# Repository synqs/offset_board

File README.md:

# offset_board
 A precise offset board used for active magnetic field control.

# Main component: AD524 and AD588 

# FEATURES:

Low drift: 1.5 ppm/°C
Low initial error: 1 mV
Pin programmable output
+10 V, +5 V, ±5 V tracking, −5 V, −10 V
Flexible output force and sense terminals
High impedance ground sense
Compact and easy to assemble
Expensive (good stuff never comes cheap)

# GENERAL DESCRIPTION: 

This board takes in a signal between 0 and 5V which then can be subtracted by a DC voltage provided by AD588 between 0 and 5V set by the poti R2 and then amplified by the AD524. The amplification factor can be set to 10,100 or 1000. 

# SPECIFICATIONS
Typical at 25°C, -12 V to 12 V output, VS = ±15 V, unless otherwise noted.

# REVISION HISTORY

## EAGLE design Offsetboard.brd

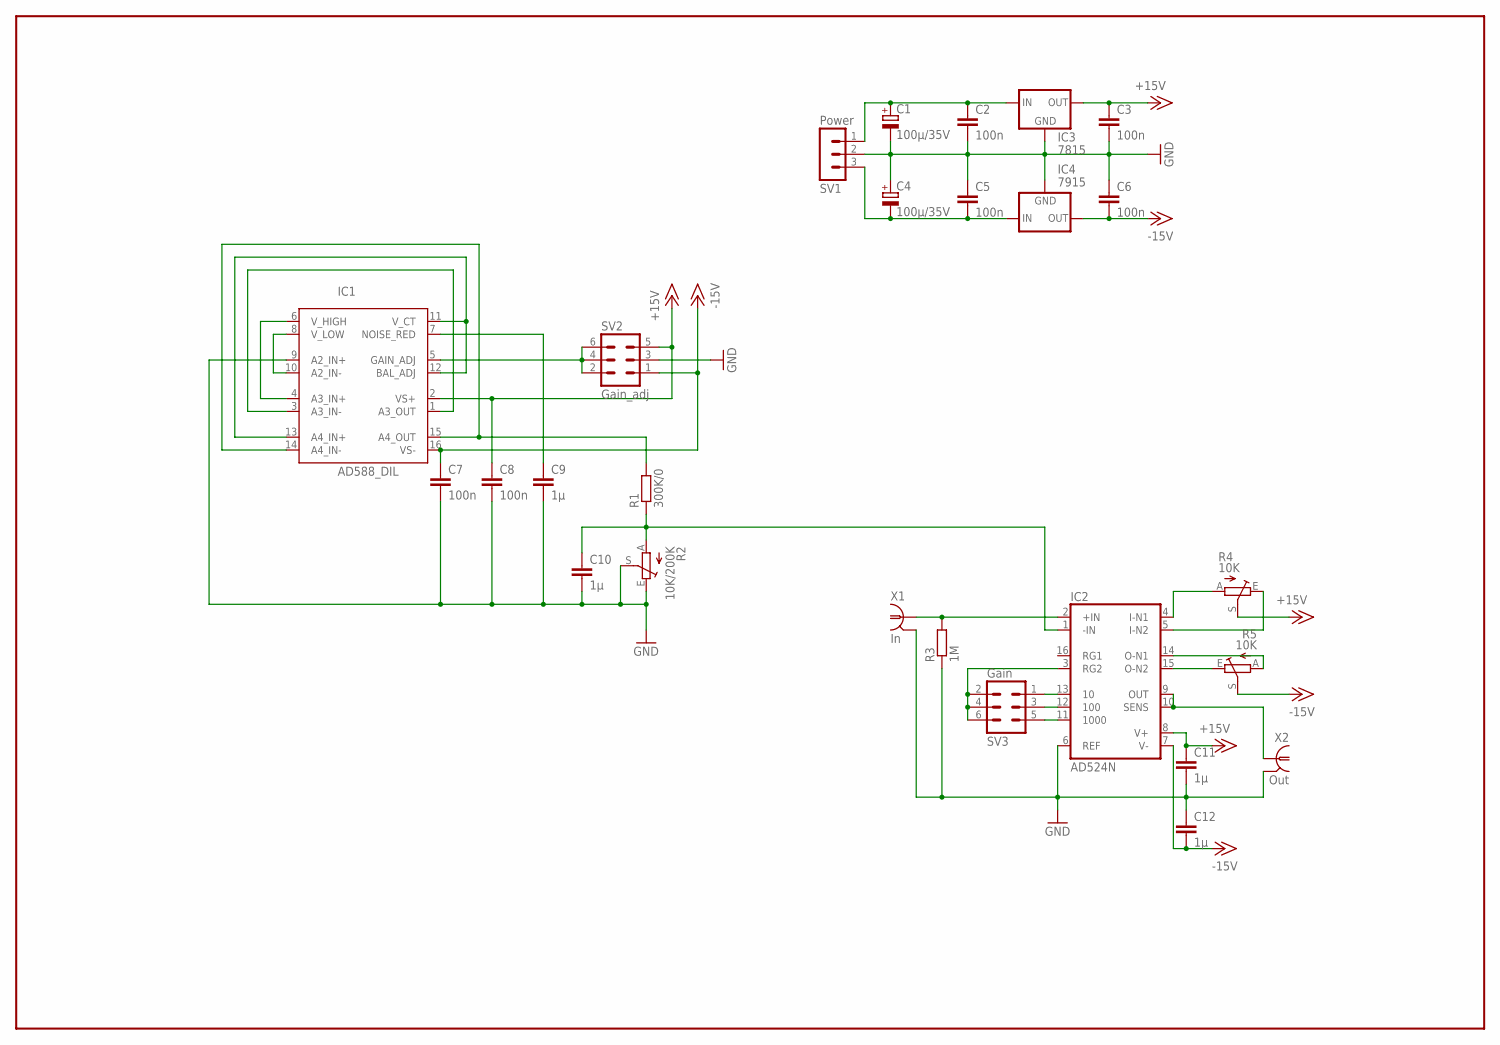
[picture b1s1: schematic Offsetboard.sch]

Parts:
C1, C4: 100µ/35V; E2,5-6
C2, C3, C5, C6, C7, C8: 100n; C1206K
C9, C10, C11, C12: 1µ; C1206K
IC1: AD588_DIL; DIL16
IC2: AD524N; DIL16
IC3: 7815; 78MXXS
IC4: 7915; 79XXS
R1: 300K/0; 0207/10
R2: 10K/200K; S64W
R3: 1M; 0207/10
R4, R5: 10K; S64W
SV1: Power; MA03-1
SV2: Gain_adj; MA03-2
SV3: Gain; MA03-2
X1: In; AMP_227161
X2: Out; AMP_227161

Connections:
+15V: C3.1, C8.1, C11.1, IC1.2 (VS+), IC2.8 (V+), IC3.OUT, R4.S, SV2.5
-15V: C6.2, C7.1, C12.2, IC1.16 (VS-), IC2.7 (V-), IC4.OUT, R5.S, SV2.1
GND: C1.-, C2.2, C3.2, C4.+, C5.1, C6.1, C7.2, C8.2, C9.2, C10.2, C11.2, C12.1, IC1.9 (A2_IN+), IC2.6 (REF), IC3.GND, IC4.GND, R2.E, R2.S, R3.1, SV1.2, SV2.3, X1.2 (GND), X2.2 (GND)
unnamed: IC2.4 (I-N1), R4.A
unnamed: IC2.15 (O-N2), R5.E
unnamed: IC2.14 (O-N1), R5.A
unnamed: IC2.5 (I-N2), R4.E
unnamed: IC2.2 (+IN), R3.2, X1.1
unnamed: IC2.13 (10), SV3.1
unnamed: IC2.12 (100), SV3.3
unnamed: IC2.11 (1000), SV3.5
unnamed: IC2.3 (RG2), SV3.2, SV3.4, SV3.6
unnamed: IC2.9 (OUT), IC2.10 (SENS), X2.1
unnamed: IC1.14 (A4_IN-), IC1.15 (A4_OUT), R1.2
unnamed: C10.1, IC2.1 (-IN), R1.1, R2.A
unnamed: IC1.1 (A3_OUT), IC1.3 (A3_IN-)
unnamed: IC1.4 (A3_IN+), IC1.6 (V_HIGH)
unnamed: C9.1, IC1.7 (NOISE_RED)
unnamed: IC1.8 (V_LOW), IC1.10 (A2_IN-)
unnamed: IC1.11 (V_CT), IC1.12 (BAL_ADJ), IC1.13 (A4_IN+)
unnamed: C4.-, C5.2, IC4.IN, SV1.3
unnamed: IC1.5 (GAIN_ADJ), SV2.2, SV2.4, SV2.6
unnamed: C1.+, C2.1, IC3.IN, SV1.1

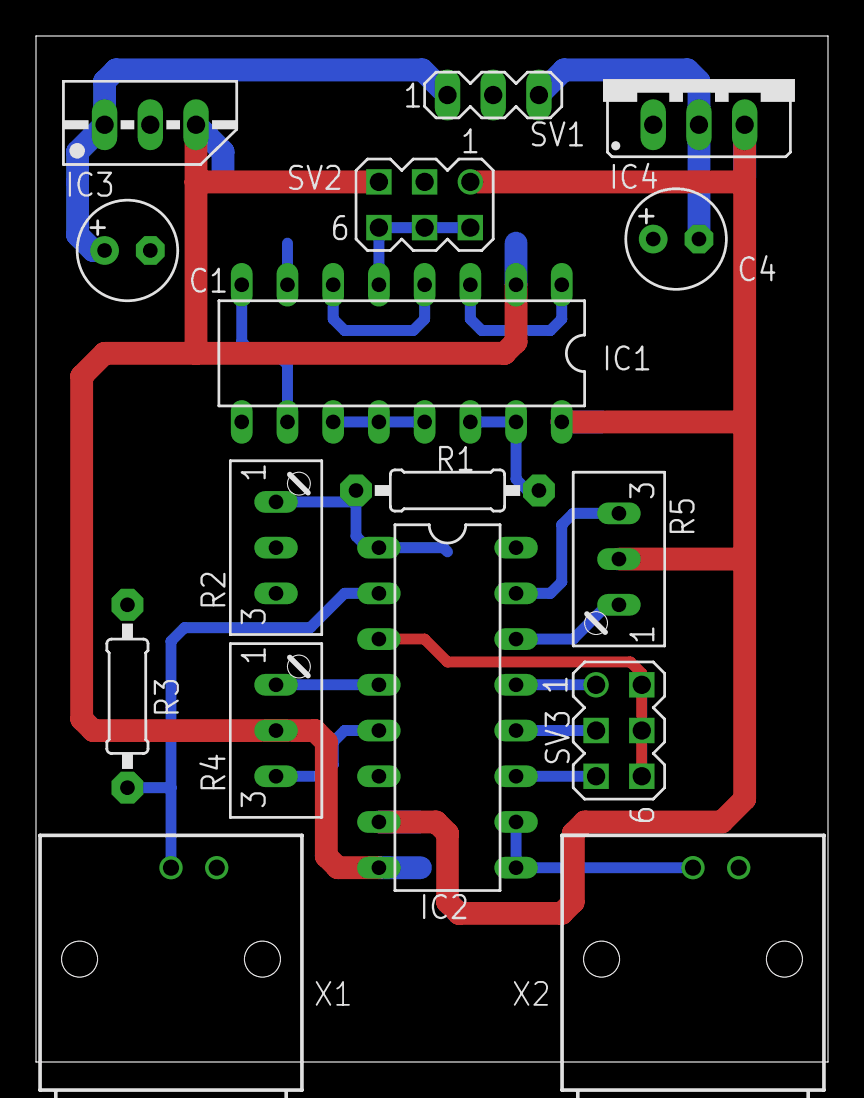
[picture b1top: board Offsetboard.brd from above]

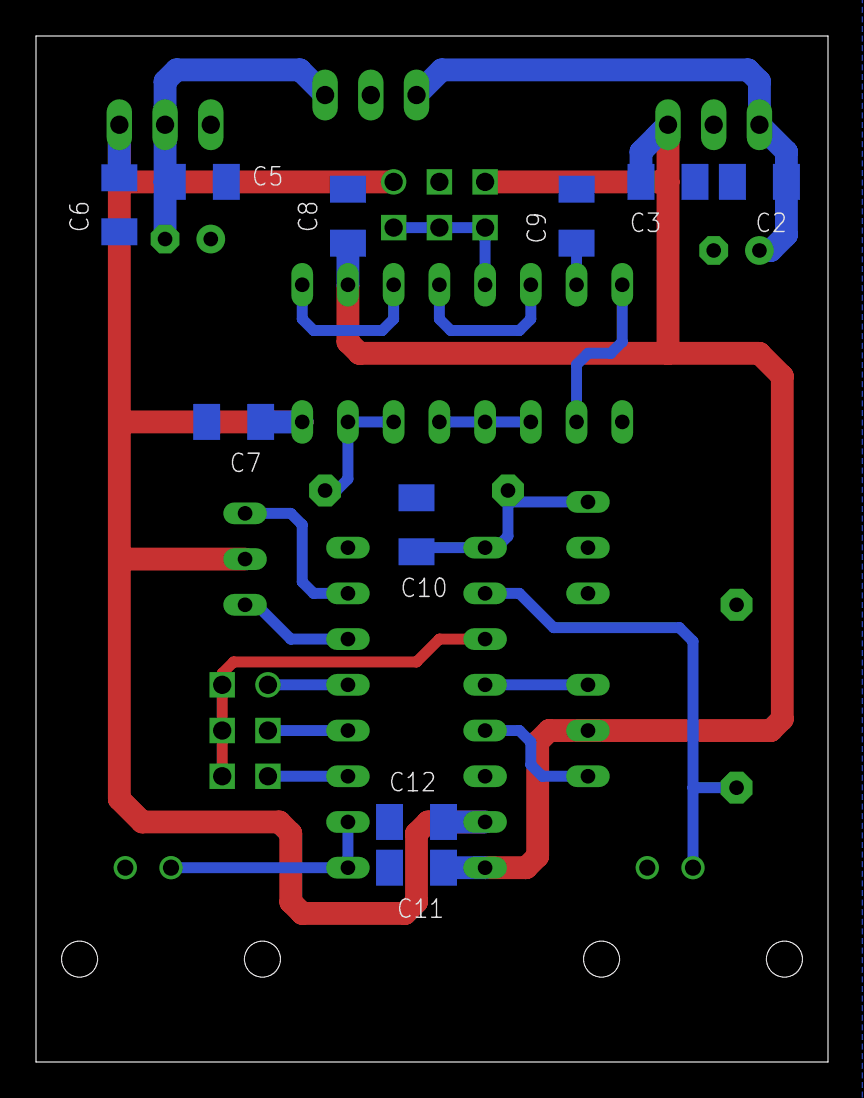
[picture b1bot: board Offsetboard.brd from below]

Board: 2 copper layers, 44.0 x 57.0 mm, 26 parts (10 on the bottom side), 23 nets.

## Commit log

2021-04-27 Added files
